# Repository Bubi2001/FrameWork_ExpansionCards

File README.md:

# FrameWork_ExpansionCards
Framework Laptop Expansion Cards

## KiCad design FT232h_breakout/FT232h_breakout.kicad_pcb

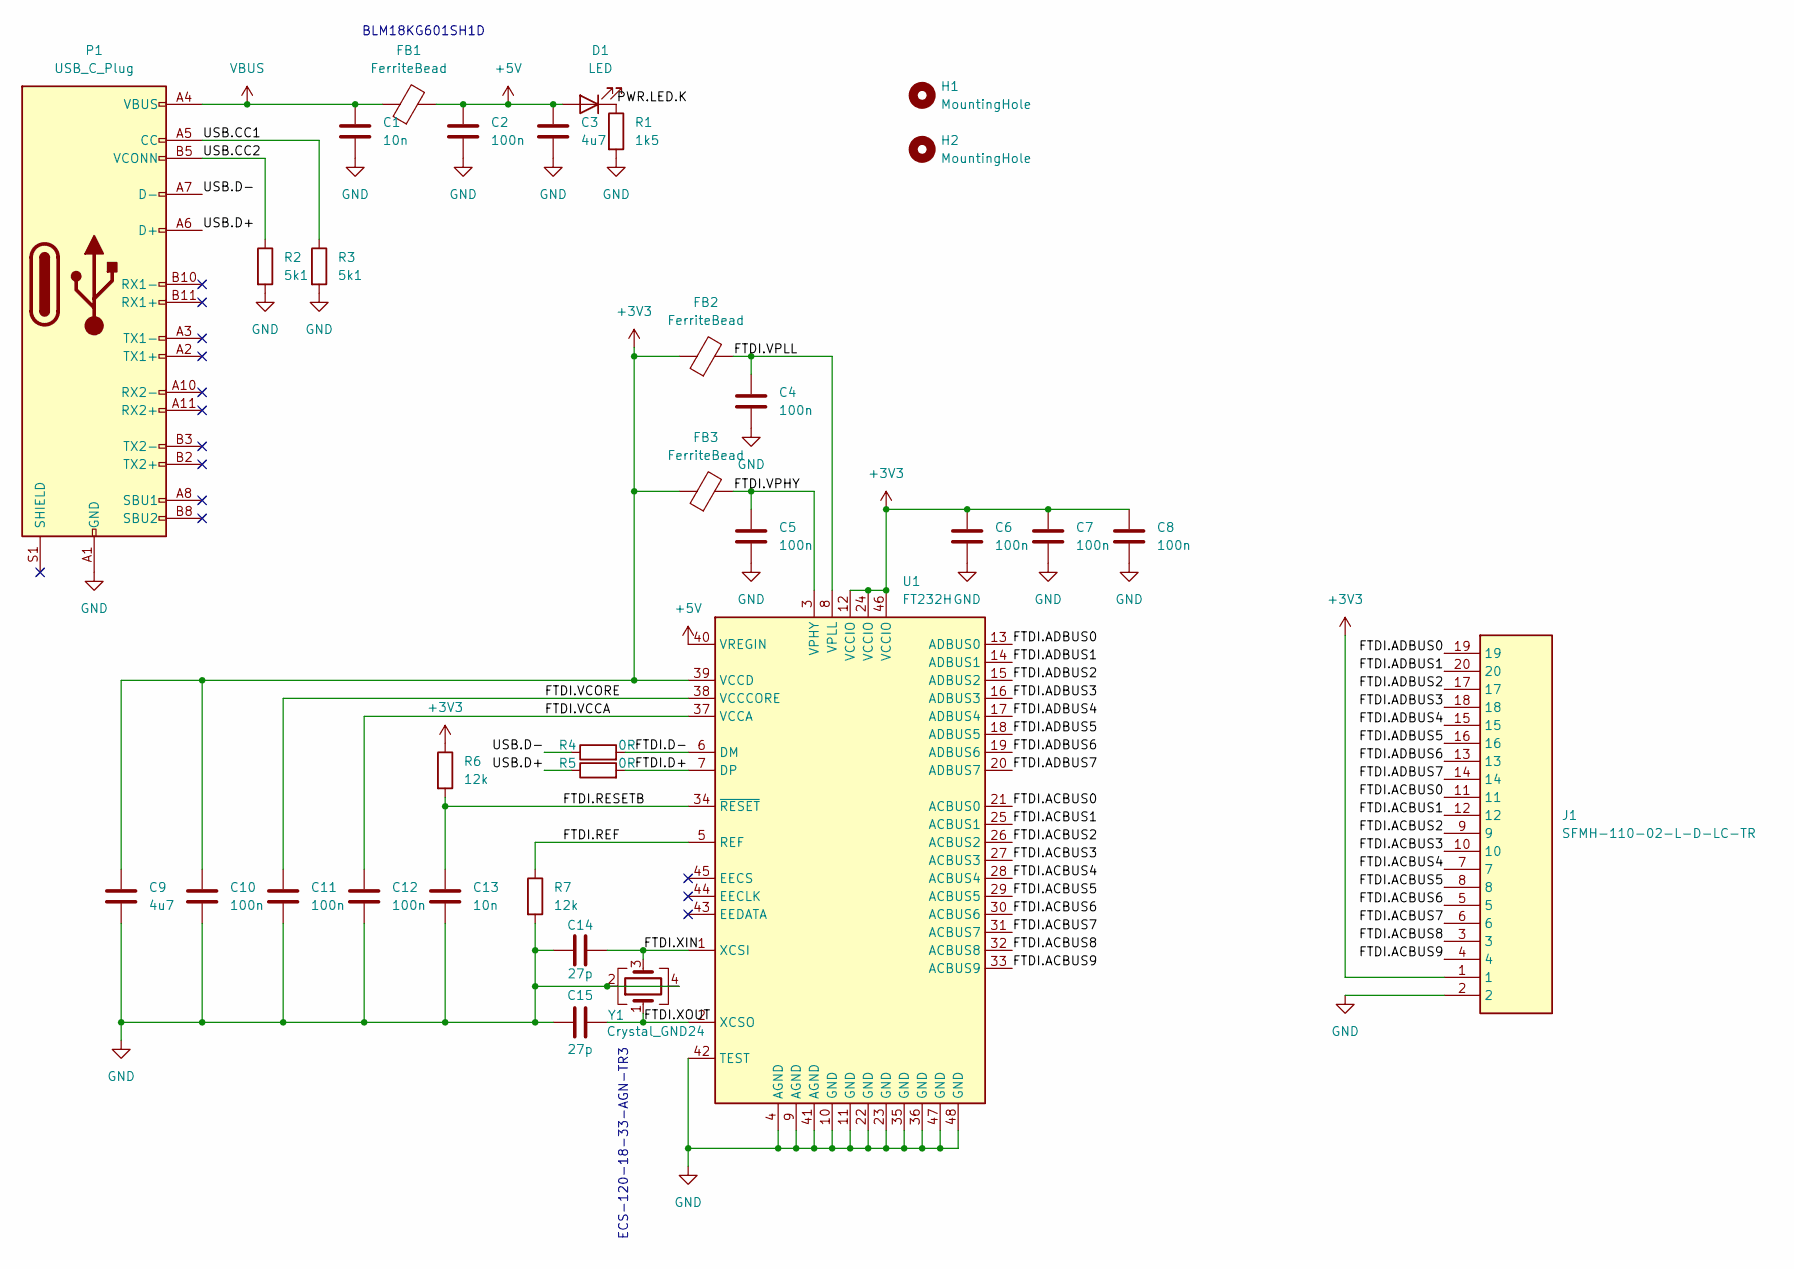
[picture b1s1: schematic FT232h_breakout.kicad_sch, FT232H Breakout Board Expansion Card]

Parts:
C1, C13: 10n; C_0603_1608Metric_Pad1.08x0.95mm_HandSolder
C2, C4, C5, C6, C7, C8, C10, C11, C12: 100n; C_0603_1608Metric_Pad1.08x0.95mm_HandSolder
C3, C9: 4u7; C_0603_1608Metric_Pad1.08x0.95mm_HandSolder
C14, C15: 27p; C_0603_1608Metric_Pad1.08x0.95mm_HandSolder
D1: LED; LED_0805_2012Metric_Pad1.15x1.40mm_HandSolder
FB1, FB2, FB3: FerriteBead; L_0603_1608Metric_Pad1.05x0.95mm_HandSolder
H1, H2: MountingHole; MountingHole_2.2mm_M2
J1: SFMH-110-02-L-D-LC-TR; SFMH11002LDLCTR; Mouser Part Number 200-SFMH11002LDLCTR
P1: USB_C_Plug; USB_C_Plug_Molex_105444
R1: 1k5; R_0603_1608Metric_Pad0.98x0.95mm_HandSolder
R2, R3: 5k1; R_0603_1608Metric_Pad0.98x0.95mm_HandSolder
R4, R5: 0R; R_0402_1005Metric_Pad0.72x0.64mm_HandSolder
R6, R7: 12k; R_0603_1608Metric_Pad0.98x0.95mm_HandSolder
U1: FT232H; LQFP-48_7x7mm_P0.5mm
Y1: Crystal_GND24; Crystal_SMD_3225-4Pin_3.2x2.5mm_HandSoldering

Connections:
+3V3: C6.1, C7.1, C8.1, C9.1, C10.1, FB2.1, FB3.1, J1.1, R6.1, U1.12 (VCCIO), U1.24 (VCCIO), U1.39 (VCCD), U1.46 (VCCIO)
+5V: C2.1, C3.1, D1.2 (A), FB1.2, U1.40 (VREGIN)
/FTDI.ACBUS0: J1.11, U1.21 (ACBUS0)
/FTDI.ACBUS1: J1.12, U1.25 (ACBUS1)
/FTDI.ACBUS2: J1.9, U1.26 (ACBUS2)
/FTDI.ACBUS3: J1.10, U1.27 (ACBUS3)
/FTDI.ACBUS4: J1.7, U1.28 (ACBUS4)
/FTDI.ACBUS5: J1.8, U1.29 (ACBUS5)
/FTDI.ACBUS6: J1.5, U1.30 (ACBUS6)
/FTDI.ACBUS7: J1.6, U1.31 (ACBUS7)
/FTDI.ACBUS8: J1.3, U1.32 (ACBUS8)
/FTDI.ACBUS9: J1.4, U1.33 (ACBUS9)
/FTDI.ADBUS0: J1.19, U1.13 (ADBUS0)
/FTDI.ADBUS1: J1.20, U1.14 (ADBUS1)
/FTDI.ADBUS2: J1.17, U1.15 (ADBUS2)
/FTDI.ADBUS3: J1.18, U1.16 (ADBUS3)
/FTDI.ADBUS4: J1.15, U1.17 (ADBUS4)
/FTDI.ADBUS5: J1.16, U1.18 (ADBUS5)
/FTDI.ADBUS6: J1.13, U1.19 (ADBUS6)
/FTDI.ADBUS7: J1.14, U1.20 (ADBUS7)
/FTDI.D+: R5.2, U1.7 (DP)
/FTDI.D-: R4.2, U1.6 (DM)
/FTDI.REF: R7.1, U1.5 (REF)
/FTDI.RESETB: C13.1, R6.2, U1.34 (~RESET)
/FTDI.VCCA: C12.1, U1.37 (VCCA)
/FTDI.VCORE: C11.1, U1.38 (VCCCORE)
/FTDI.VPHY: C5.1, FB3.2, U1.3 (VPHY)
/FTDI.VPLL: C4.1, FB2.2, U1.8 (VPLL)
/FTDI.XIN: C14.2, U1.1 (XCSI), Y1.3
/FTDI.XOUT: C15.2, U1.2 (XCSO), Y1.1
/PWR.LED.K: D1.1 (K), R1.1
/USB.CC1: P1.A5 (CC), R3.1
/USB.CC2: P1.B5 (VCONN), R2.1
/USB.D+: P1.A6 (D+), R5.1
/USB.D-: P1.A7 (D-), R4.1
GND: C1.2, C2.2, C3.2, C4.2, C5.2, C6.2, C7.2, C8.2, C9.2, C10.2, C11.2, C12.2, C13.2, C14.1, C15.1, J1.2, P1.A1 (GND), P1.A12 (GND), P1.B1 (GND), P1.B12 (GND), R1.2, R2.2, R3.2, R7.2, U1.4 (AGND), U1.9 (AGND), U1.10 (GND), U1.11 (GND), U1.22 (GND), U1.23 (GND), U1.35 (GND), U1.36 (GND), U1.41 (AGND), U1.42 (TEST), U1.47 (GND), U1.48 (GND), Y1.2, Y1.4
VBUS: C1.1, FB1.1, P1.A4 (VBUS), P1.A9 (VBUS), P1.B4 (VBUS), P1.B9 (VBUS)

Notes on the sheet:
ECS-120-18-33-AGN-TR3
BLM18KG601SH1D

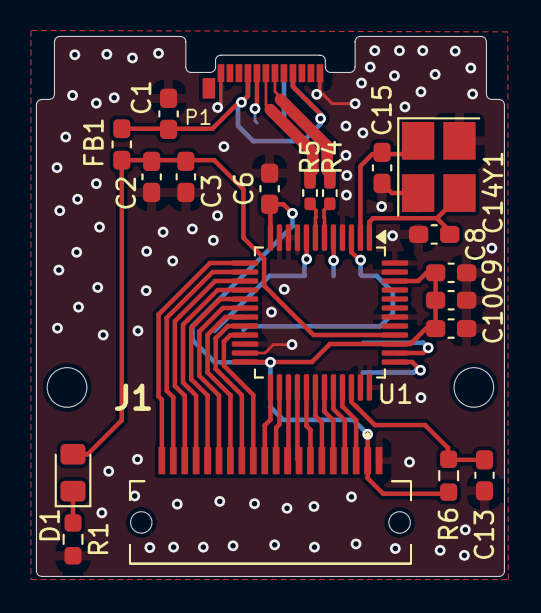
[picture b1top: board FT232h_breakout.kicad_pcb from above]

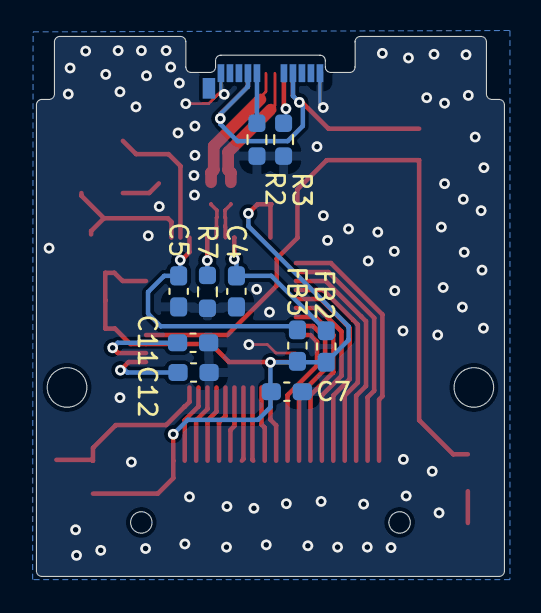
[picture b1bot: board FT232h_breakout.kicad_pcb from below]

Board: 2 copper layers, 26.0 x 30.0 mm, 32 parts (10 on the bottom side), 37 nets.

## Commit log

2024-05-25 Done FT232H Breakout board
2025-02-08 added GPIO moduke
2025-02-09 added submodules

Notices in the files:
FT232h_breakout/FT232h_breakout.kicad_pcb:
This work is licensed under a Creative Commons Attribution 4.0 International License
